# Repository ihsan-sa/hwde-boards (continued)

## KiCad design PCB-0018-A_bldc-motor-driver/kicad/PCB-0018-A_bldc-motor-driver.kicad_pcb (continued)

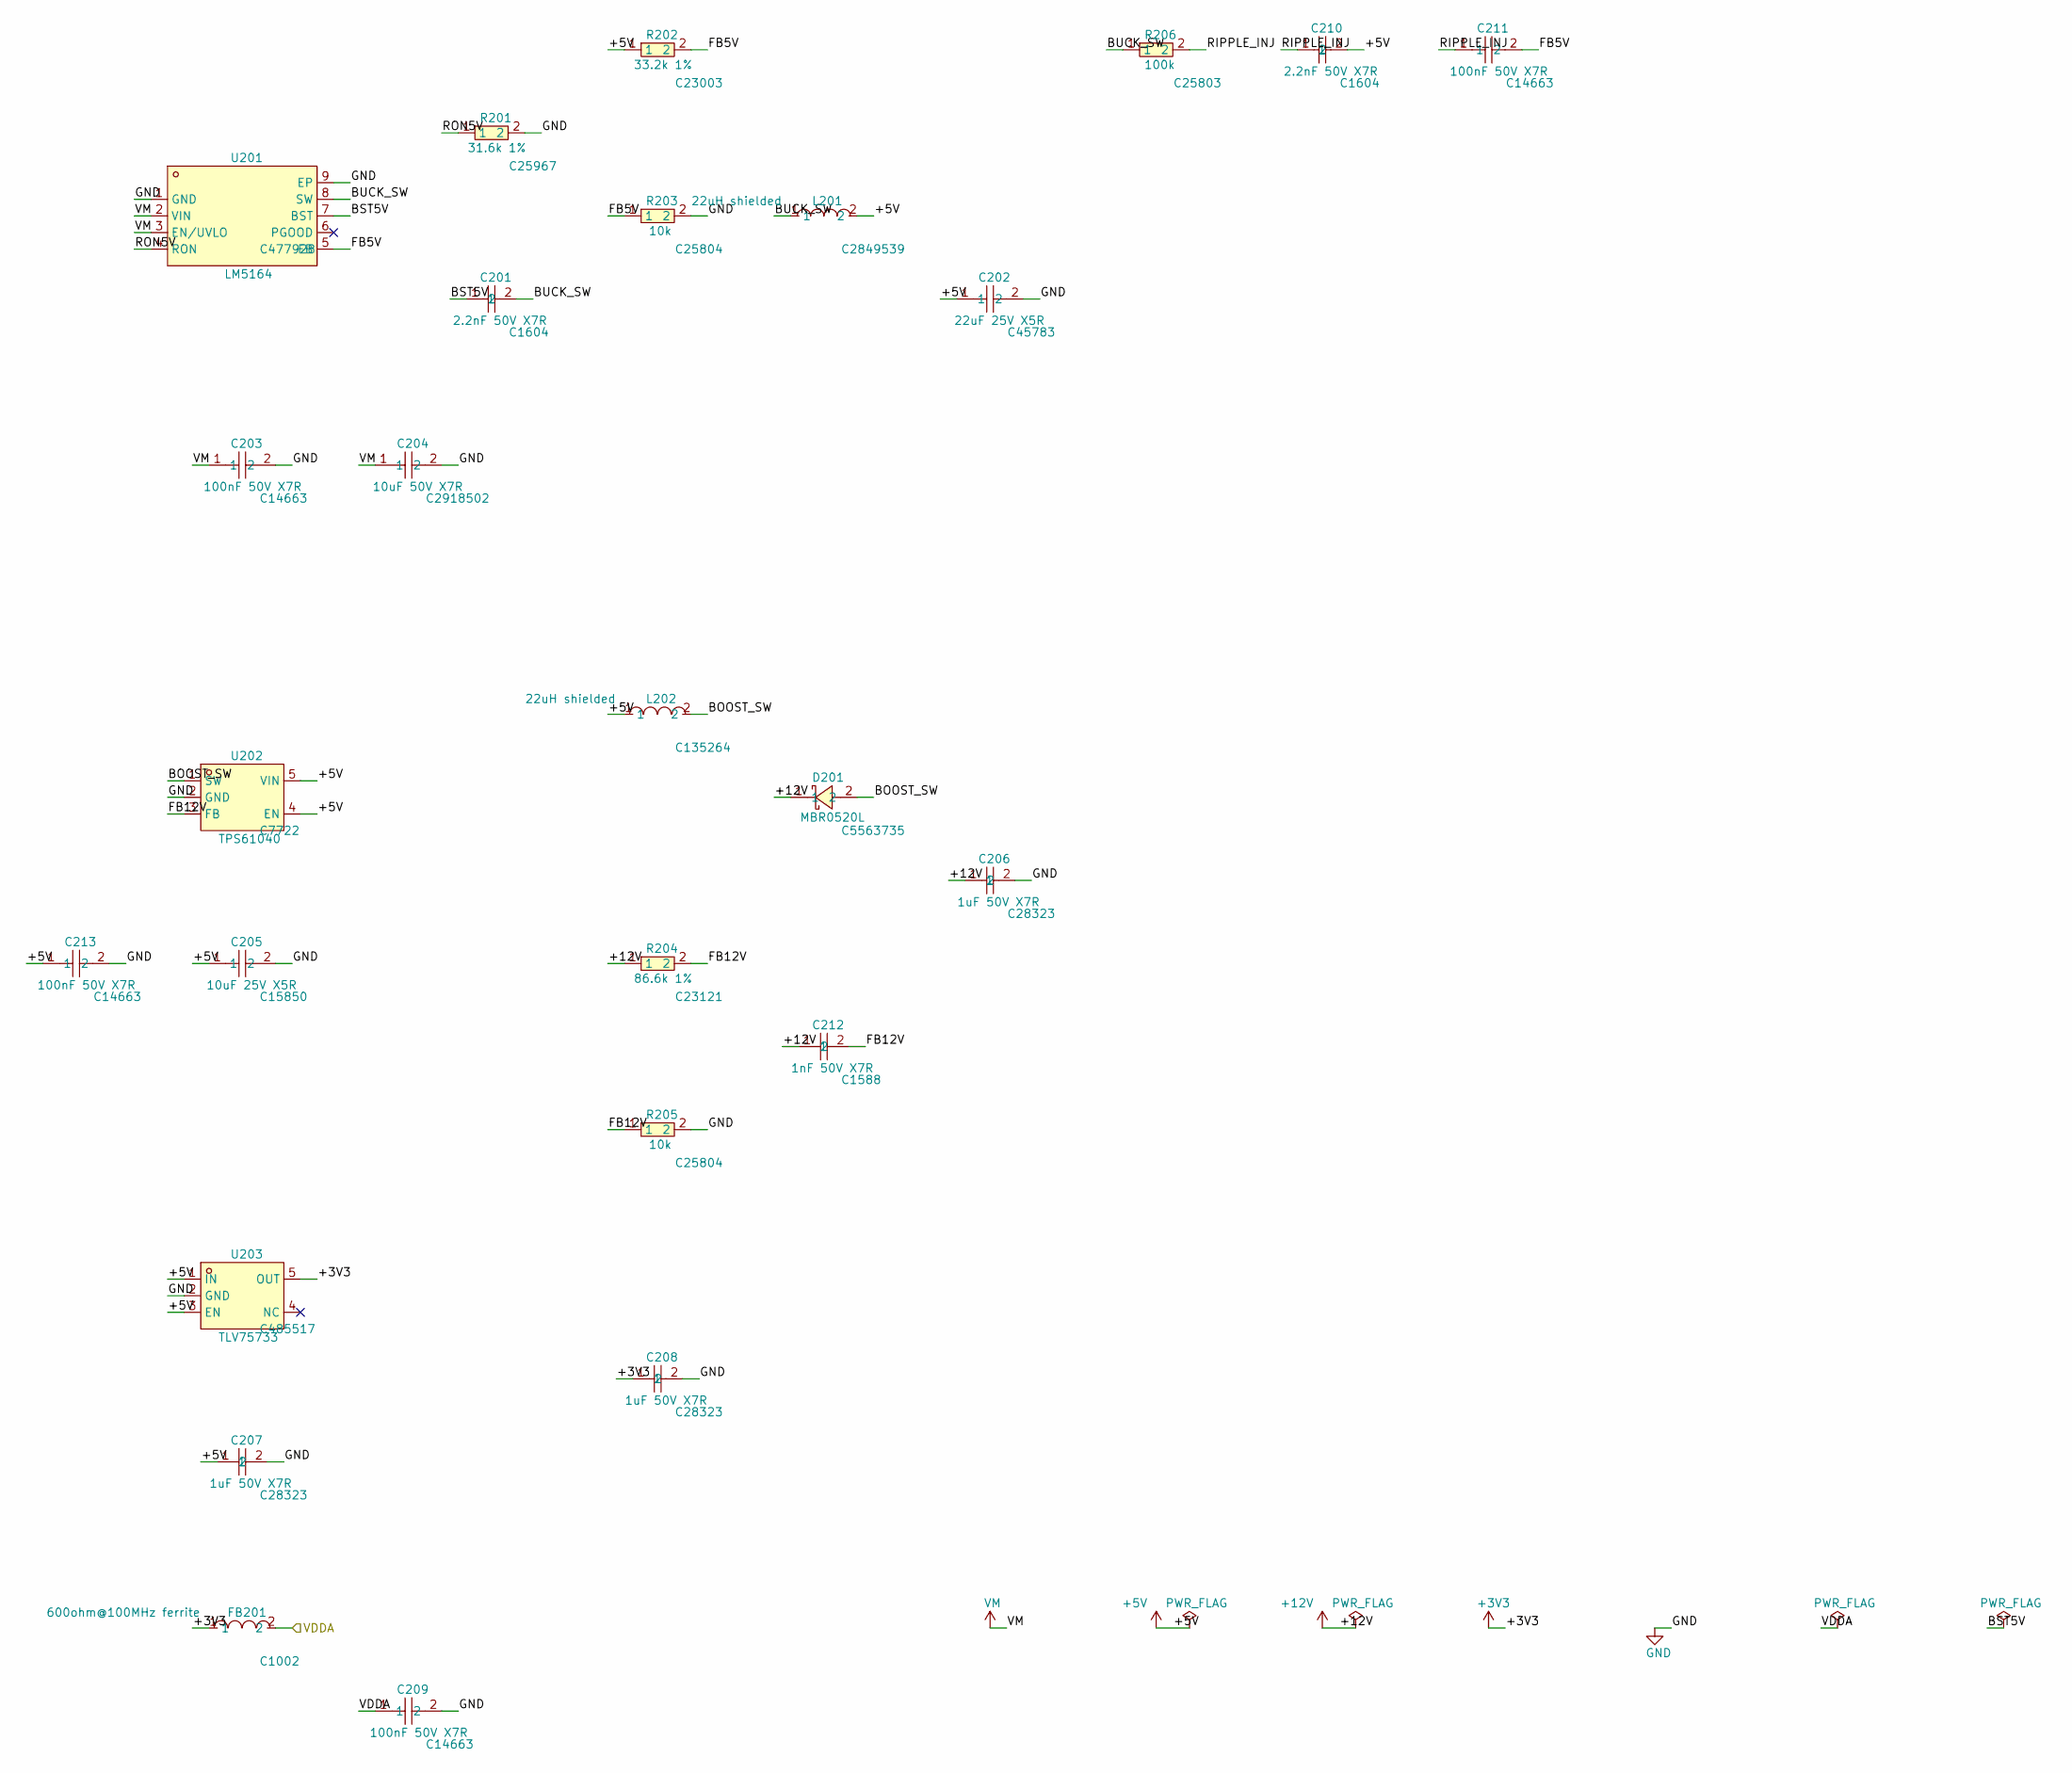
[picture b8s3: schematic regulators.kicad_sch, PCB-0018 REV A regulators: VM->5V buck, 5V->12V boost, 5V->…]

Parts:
C201, C210: 2.2nF 50V X7R; C0603; LCSC C1604
C202: 22uF 25V X5R; C0805; LCSC C45783
C203, C209, C211, C213: 100nF 50V X7R; C0603; LCSC C14663
C204: 10uF 50V X7R; C1210; LCSC C2918502
C205: 10uF 25V X5R; C0805; LCSC C15850
C206, C207, C208: 1uF 50V X7R; C0805; LCSC C28323
C212: 1nF 50V X7R; C0603; LCSC C1588
D201: MBR0520L; SOD-123_L2.7-W1.6-LS3.7-RD-1; LCSC C5563735
FB201: 600ohm@100MHz ferrite; R0603; LCSC C1002
L201: 22uH shielded; IND-SMD_L6.0-W6.0; LCSC C2849539
L202: 22uH shielded; IND-SMD_L4.0-W4.0_LQH44PN2R2MP0L; LCSC C135264
R201: 31.6k 1%; R0603; LCSC C25967
R202: 33.2k 1%; R0603; LCSC C23003
R203, R205: 10k; R0603; LCSC C25804
R204: 86.6k 1%; R0603; LCSC C23121
R206: 100k; R0603; LCSC C25803
U201: LM5164; SO-8_L4.9-W3.9-P1.27-LS6.0-BL-EP; LCSC C477928
U202: TPS61040; SOT-23-5_L2.9-W1.6-P0.95-LS2.8-BL; LCSC C7722
U203: TLV75733; SOT-23-5_L2.9-W1.6-P0.95-LS2.8-BL; LCSC C485517

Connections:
+3V3: C208.1, FB201.1, U203.5 (OUT); also elsewhere on the board
+5V: C202.1, C205.1, C207.1, C210.2, C213.1, L201.2, L202.1, R202.1, U202.4 (EN), U202.5 (VIN), U203.1 (IN), U203.3 (EN); also elsewhere on the board
+12V: C206.1, C212.1, D201.1, R204.1; also elsewhere on the board
/VDDA: C209.1, FB201.2; also elsewhere on the board
/regulators/BOOST_SW: D201.2, L202.2, U202.1 (SW)
/regulators/BST5V: C201.1, U201.7 (BST)
/regulators/BUCK_SW: C201.2, L201.1, R206.1, U201.8 (SW)
/regulators/FB5V: C211.2, R202.2, R203.1, U201.5 (FB)
/regulators/FB12V: C212.2, R204.2, R205.1, U202.3 (FB)
/regulators/RIPPLE_INJ: C210.1, C211.1, R206.2
/regulators/RON5V: R201.1, U201.4 (RON)
GND: C202.2, C203.2, C204.2, C205.2, C206.2, C207.2, C208.2, C209.2, C213.2, R201.2, R203.2, R205.2, U201.1 (GND), U201.9 (EP), U202.2 (GND), U203.2 (GND); also elsewhere on the board
VM: C203.1, C204.1, U201.2 (VIN), U201.3 (EN/UVLO); also elsewhere on the board

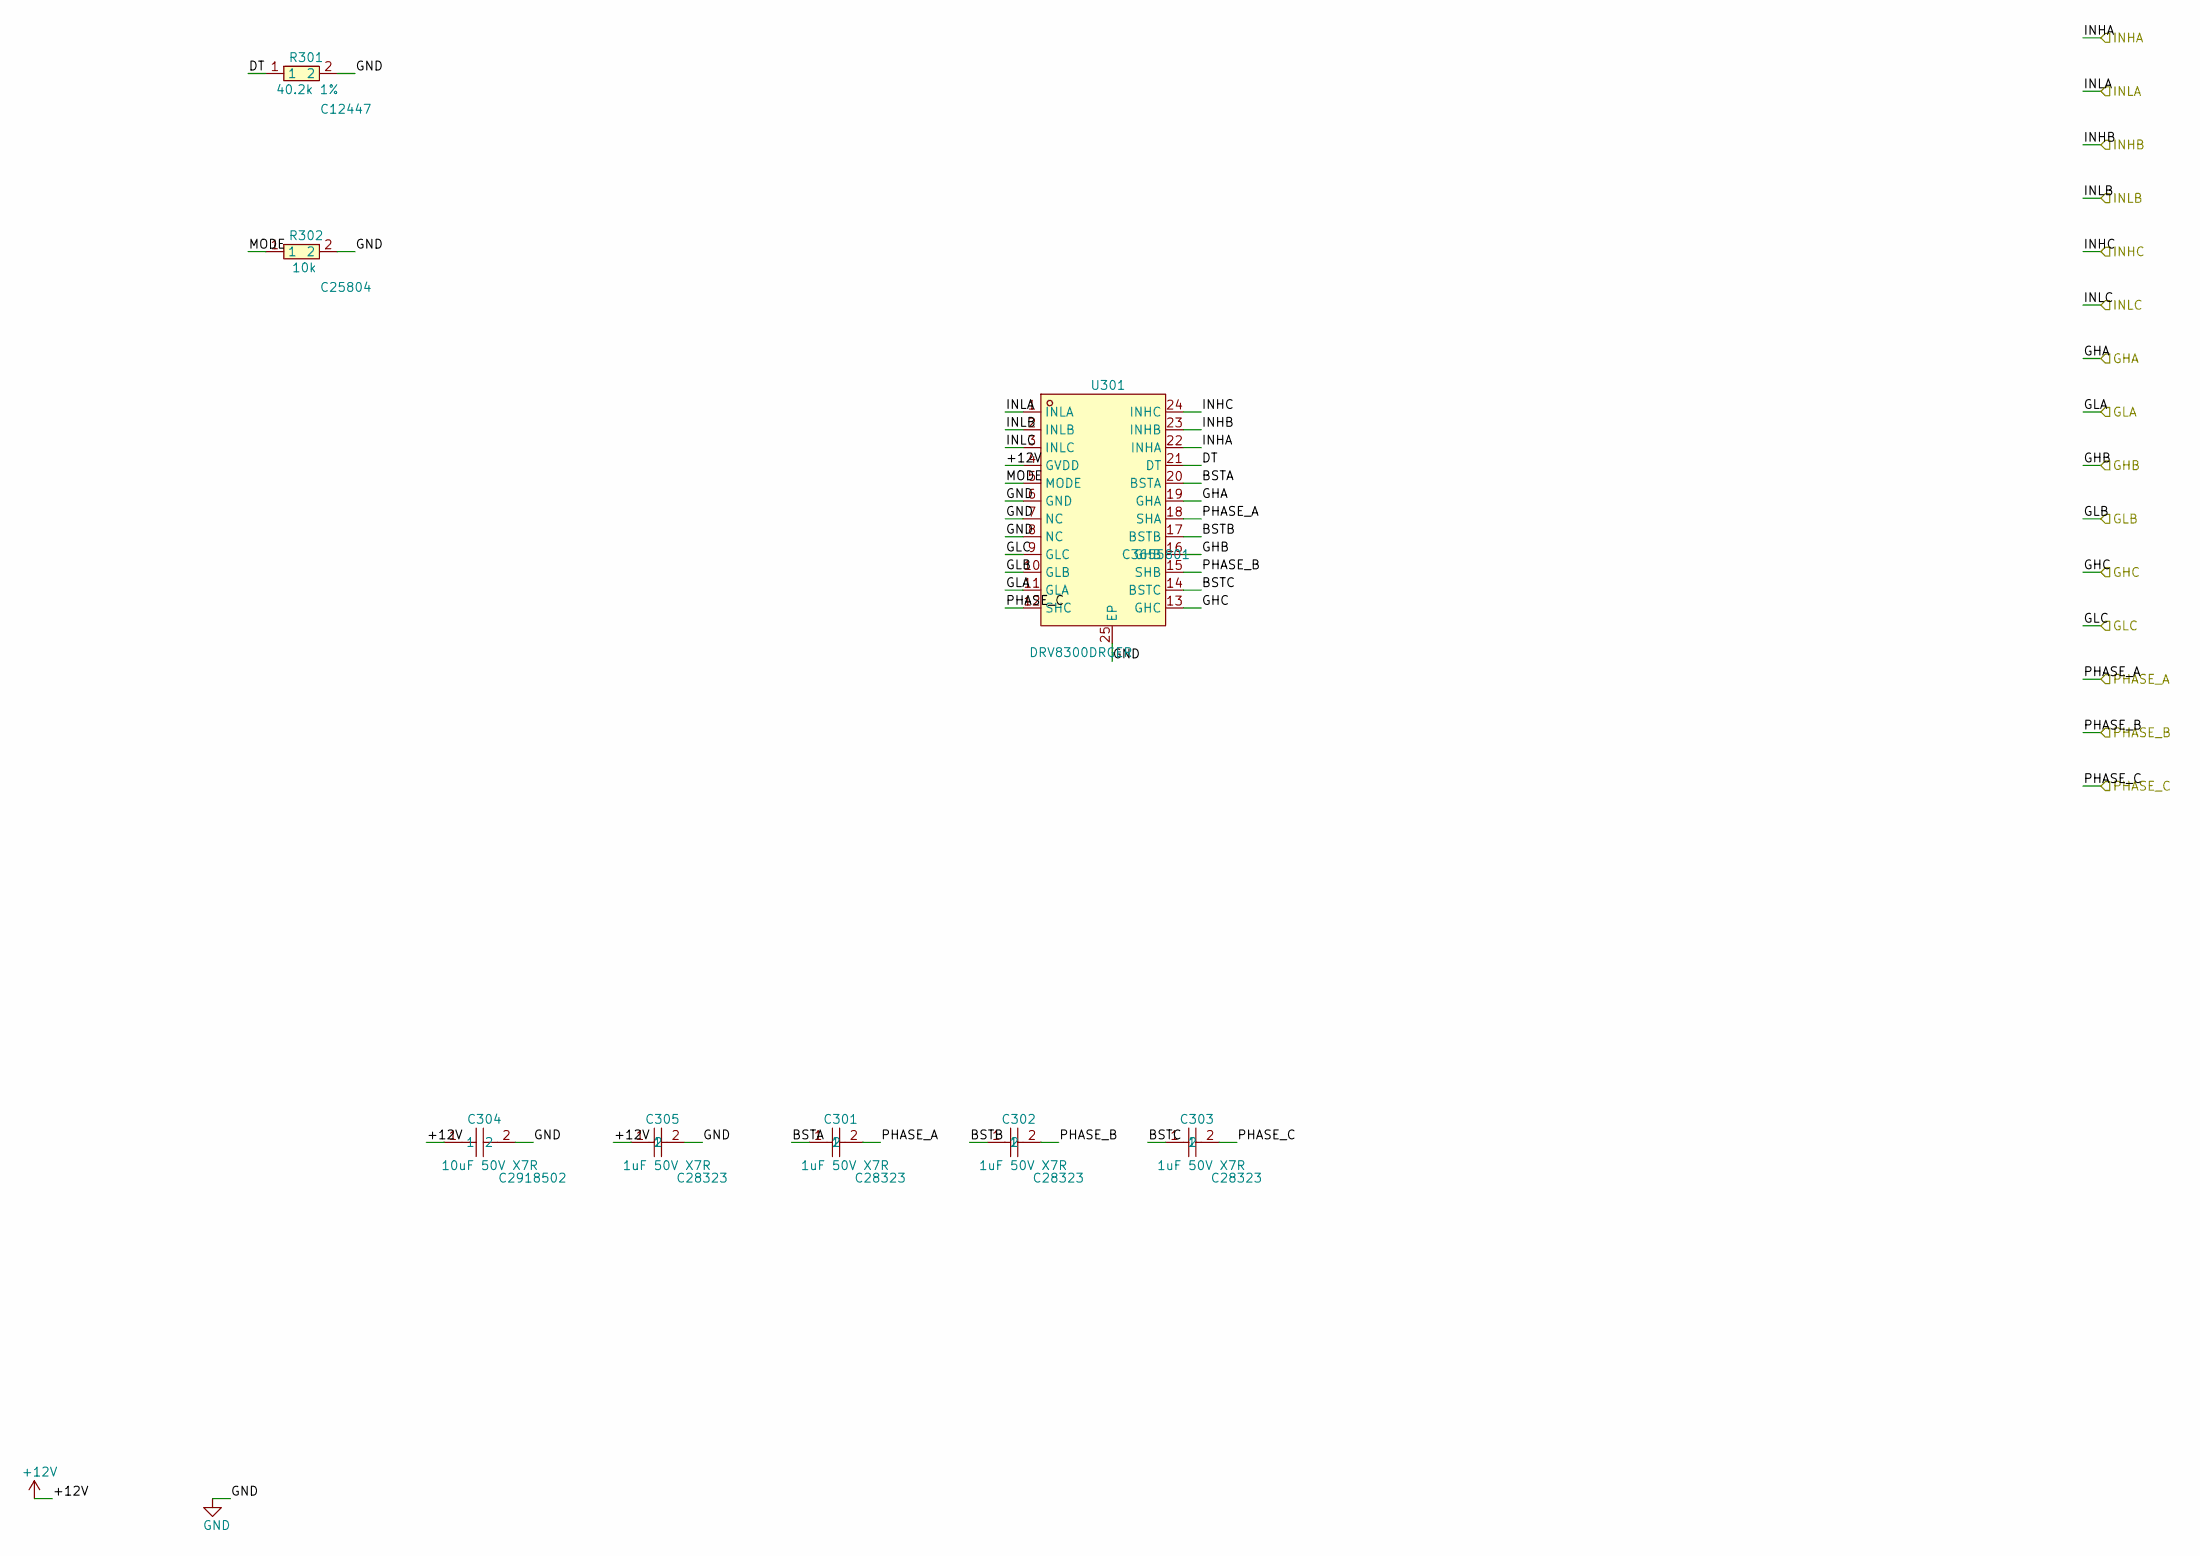
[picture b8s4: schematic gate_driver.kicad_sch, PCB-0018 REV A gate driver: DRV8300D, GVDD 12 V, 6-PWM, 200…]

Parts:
C301, C302, C303, C305: 1uF 50V X7R; C0805; LCSC C28323
C304: 10uF 50V X7R; C1210; LCSC C2918502
R301: 40.2k 1%; R0603; LCSC C12447
R302: 10k; R0603; LCSC C25804
U301: DRV8300DRGER; VQFN-24_L4.0-W4.0-P0.50-TL-EP2.5; LCSC C3655801

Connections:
+12V: C304.1, C305.1, U301.4 (GVDD); also elsewhere on the board
/GHA: U301.19 (GHA); also elsewhere on the board
/GHB: U301.16 (GHB); also elsewhere on the board
/GHC: U301.13 (GHC); also elsewhere on the board
/GLA: U301.11 (GLA); also elsewhere on the board
/GLB: U301.10 (GLB); also elsewhere on the board
/GLC: U301.9 (GLC); also elsewhere on the board
/INHA: U301.22 (INHA); also elsewhere on the board
/INHB: U301.23 (INHB); also elsewhere on the board
/INHC: U301.24 (INHC); also elsewhere on the board
/INLA: U301.1 (INLA); also elsewhere on the board
/INLB: U301.2 (INLB); also elsewhere on the board
/INLC: U301.3 (INLC); also elsewhere on the board
/PHASE_A: C301.2, U301.18 (SHA); also elsewhere on the board
/PHASE_B: C302.2, U301.15 (SHB); also elsewhere on the board
/PHASE_C: C303.2, U301.12 (SHC); also elsewhere on the board
/gate_driver/BSTA: C301.1, U301.20 (BSTA)
/gate_driver/BSTB: C302.1, U301.17 (BSTB)
/gate_driver/BSTC: C303.1, U301.14 (BSTC)
/gate_driver/DT: R301.1, U301.21 (DT)
/gate_driver/MODE: R302.1, U301.5 (MODE)
GND: C304.2, C305.2, R301.2, R302.2, U301.6 (GND), U301.7 (NC), U301.8 (NC), U301.25 (EP); also elsewhere on the board

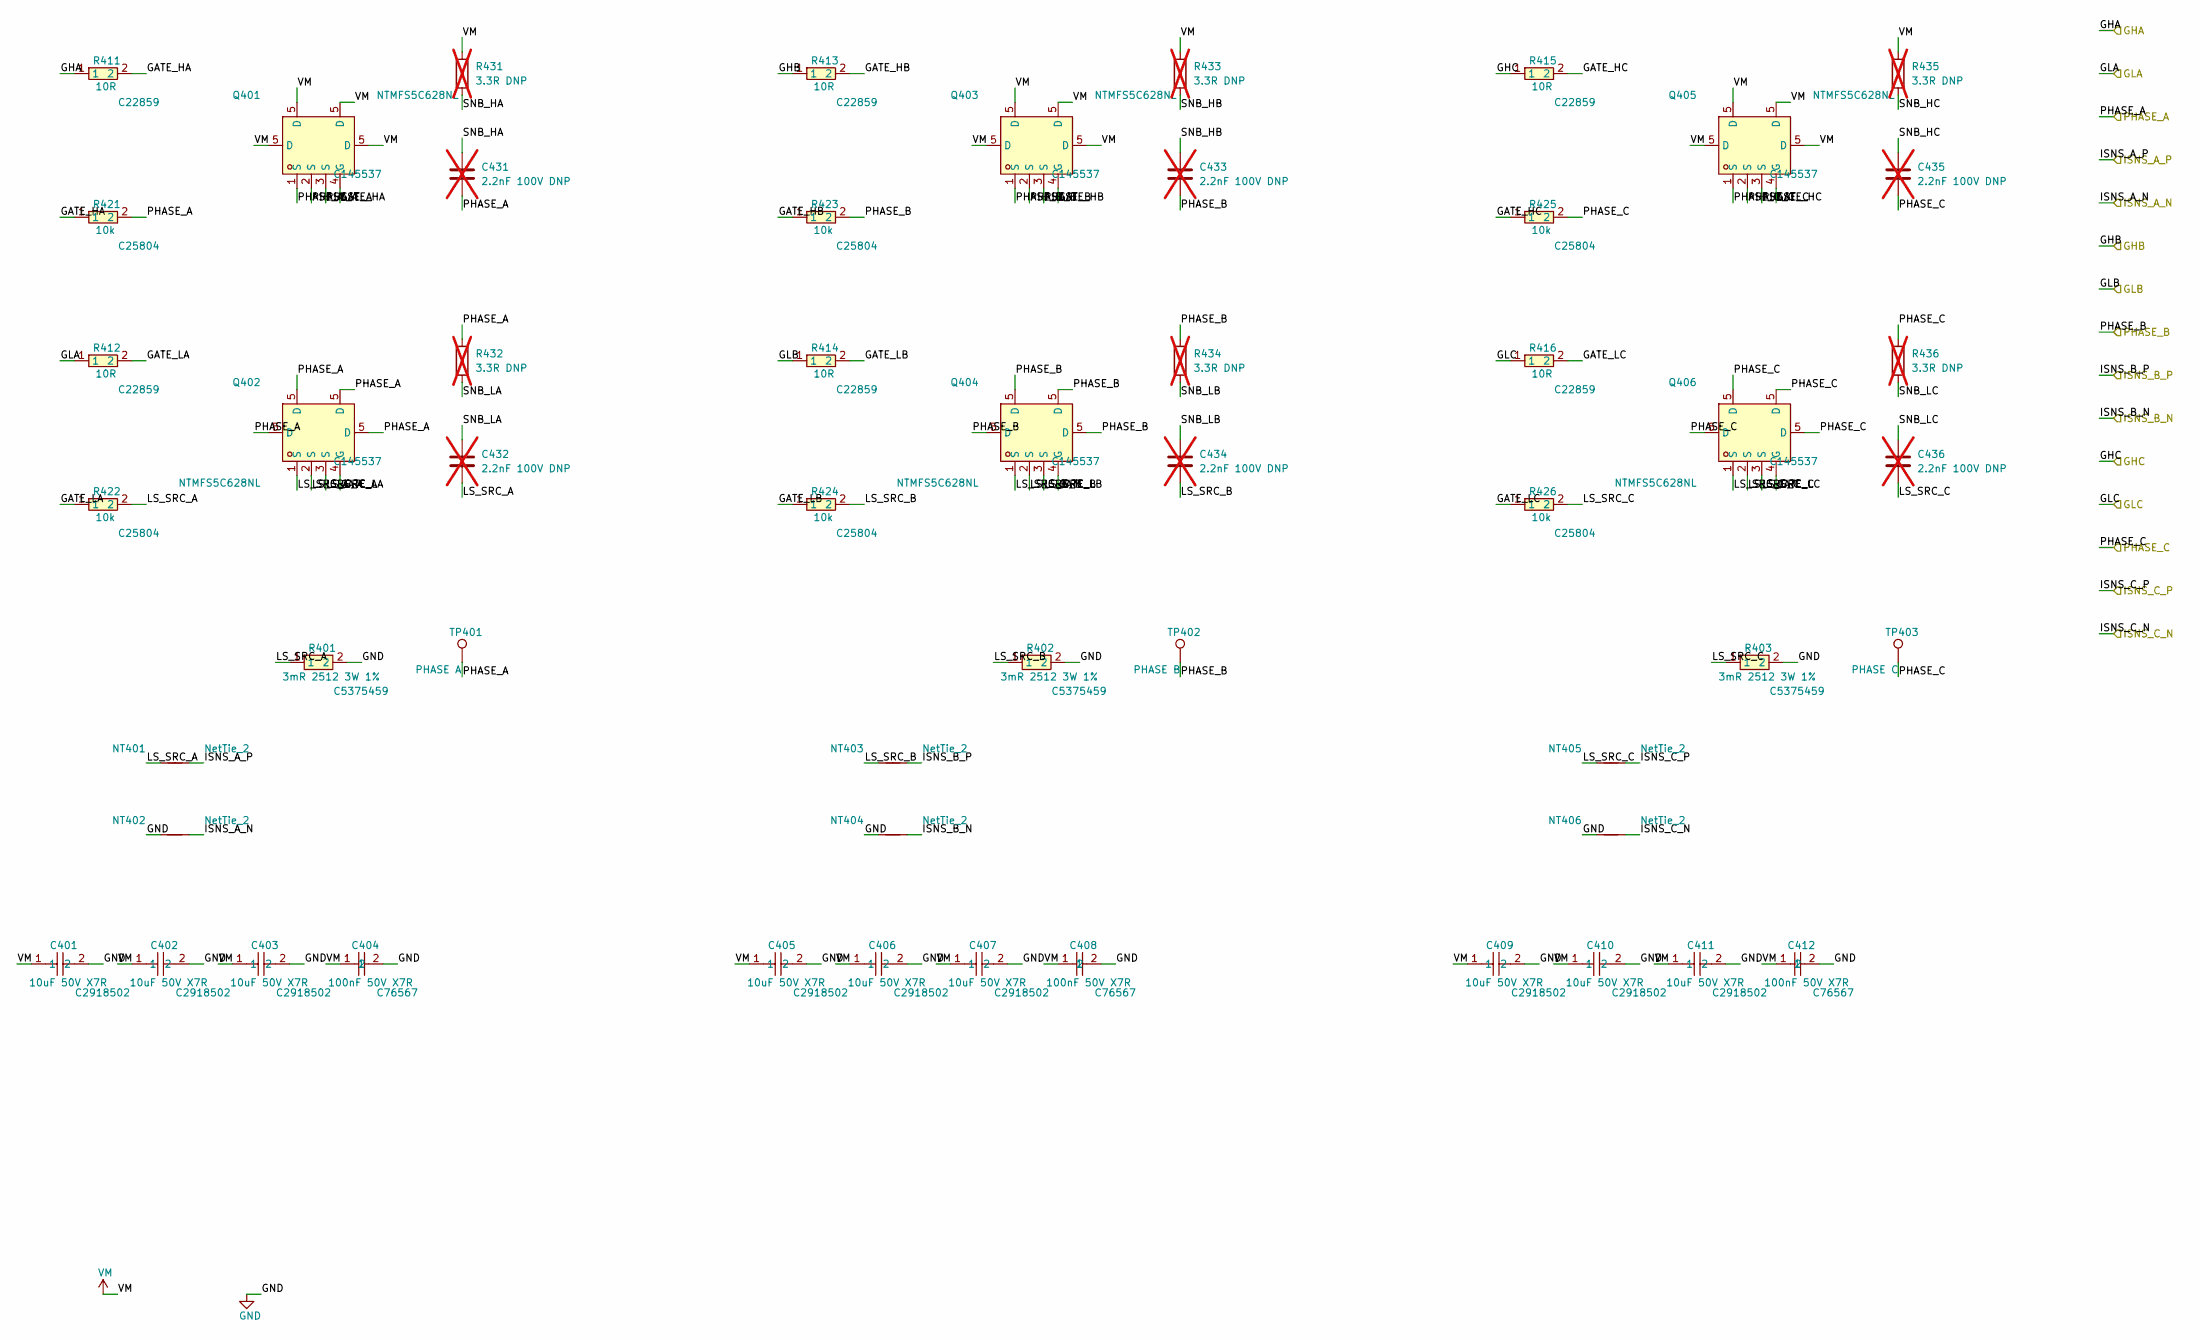
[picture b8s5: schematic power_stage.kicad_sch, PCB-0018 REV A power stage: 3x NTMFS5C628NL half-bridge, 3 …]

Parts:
C401, C402, C403, C405, C406, C407, C409, C410, C411: 10uF 50V X7R; C1210; LCSC C2918502
C404, C408, C412: 100nF 50V X7R; C1210; LCSC C76567
C431, C432, C433, C434, C435, C436: 2.2nF 100V DNP; C0603; not fitted
NT401, NT402, NT403, NT404, NT405, NT406: NetTie_2; NetTie-2_SMD_Pad0.5mm
Q401, Q402, Q403, Q404, Q405, Q406: NTMFS5C628NL; DFN-5_L4.9-W5.9-P1.27-LS6.2-BL; LCSC C145537
R401, R402, R403: 3mR 2512 3W 1%; R2512; LCSC C5375459
R411, R412, R413, R414, R415, R416: 10R; R0603; LCSC C22859
R421, R422, R423, R424, R425, R426: 10k; R0603; LCSC C25804
R431, R432, R433, R434, R435, R436: 3.3R DNP; R0603; not fitted
TP401: PHASE A; TestPoint_THTPad_4.0x4.0mm_Drill2.0mm
TP402: PHASE B; TestPoint_THTPad_4.0x4.0mm_Drill2.0mm
TP403: PHASE C; TestPoint_THTPad_4.0x4.0mm_Drill2.0mm

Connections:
/GHA: R411.1; also elsewhere on the board
/GHB: R413.1; also elsewhere on the board
/GHC: R415.1; also elsewhere on the board
/GLA: R412.1; also elsewhere on the board
/GLB: R414.1; also elsewhere on the board
/GLC: R416.1; also elsewhere on the board
/ISNS_A_N: NT402.2; also elsewhere on the board
/ISNS_A_P: NT401.2; also elsewhere on the board
/ISNS_B_N: NT404.2; also elsewhere on the board
/ISNS_B_P: NT403.2; also elsewhere on the board
/ISNS_C_N: NT406.2; also elsewhere on the board
/ISNS_C_P: NT405.2; also elsewhere on the board
/PHASE_A: C431.2, Q401.1 (S), Q401.2 (S), Q401.3 (S), Q402.5 (D), R421.2, R432.1, TP401.1; also elsewhere on the board
/PHASE_B: C433.2, Q403.1 (S), Q403.2 (S), Q403.3 (S), Q404.5 (D), R423.2, R434.1, TP402.1; also elsewhere on the board
/PHASE_C: C435.2, Q405.1 (S), Q405.2 (S), Q405.3 (S), Q406.5 (D), R425.2, R436.1, TP403.1; also elsewhere on the board
/power_stage/GATE_HA: Q401.4 (G), R411.2, R421.1
/power_stage/GATE_HB: Q403.4 (G), R413.2, R423.1
/power_stage/GATE_HC: Q405.4 (G), R415.2, R425.1
/power_stage/GATE_LA: Q402.4 (G), R412.2, R422.1
/power_stage/GATE_LB: Q404.4 (G), R414.2, R424.1
/power_stage/GATE_LC: Q406.4 (G), R416.2, R426.1
/power_stage/LS_SRC_A: C432.2, NT401.1, Q402.1 (S), Q402.2 (S), Q402.3 (S), R401.1, R422.2
/power_stage/LS_SRC_B: C434.2, NT403.1, Q404.1 (S), Q404.2 (S), Q404.3 (S), R402.1, R424.2
/power_stage/LS_SRC_C: C436.2, NT405.1, Q406.1 (S), Q406.2 (S), Q406.3 (S), R403.1, R426.2
/power_stage/SNB_HA: C431.1, R431.2
/power_stage/SNB_HB: C433.1, R433.2
/power_stage/SNB_HC: C435.1, R435.2
/power_stage/SNB_LA: C432.1, R432.2
/power_stage/SNB_LB: C434.1, R434.2
/power_stage/SNB_LC: C436.1, R436.2
GND: C401.2, C402.2, C403.2, C404.2, C405.2, C406.2, C407.2, C408.2, C409.2, C410.2, C411.2, C412.2, NT402.1, NT404.1, NT406.1, R401.2, R402.2, R403.2; also elsewhere on the board
VM: C401.1, C402.1, C403.1, C404.1, C405.1, C406.1, C407.1, C408.1, C409.1, C410.1, C411.1, C412.1, Q401.5 (D), Q403.5 (D), Q405.5 (D), R431.1, R433.1, R435.1; also elsewhere on the board

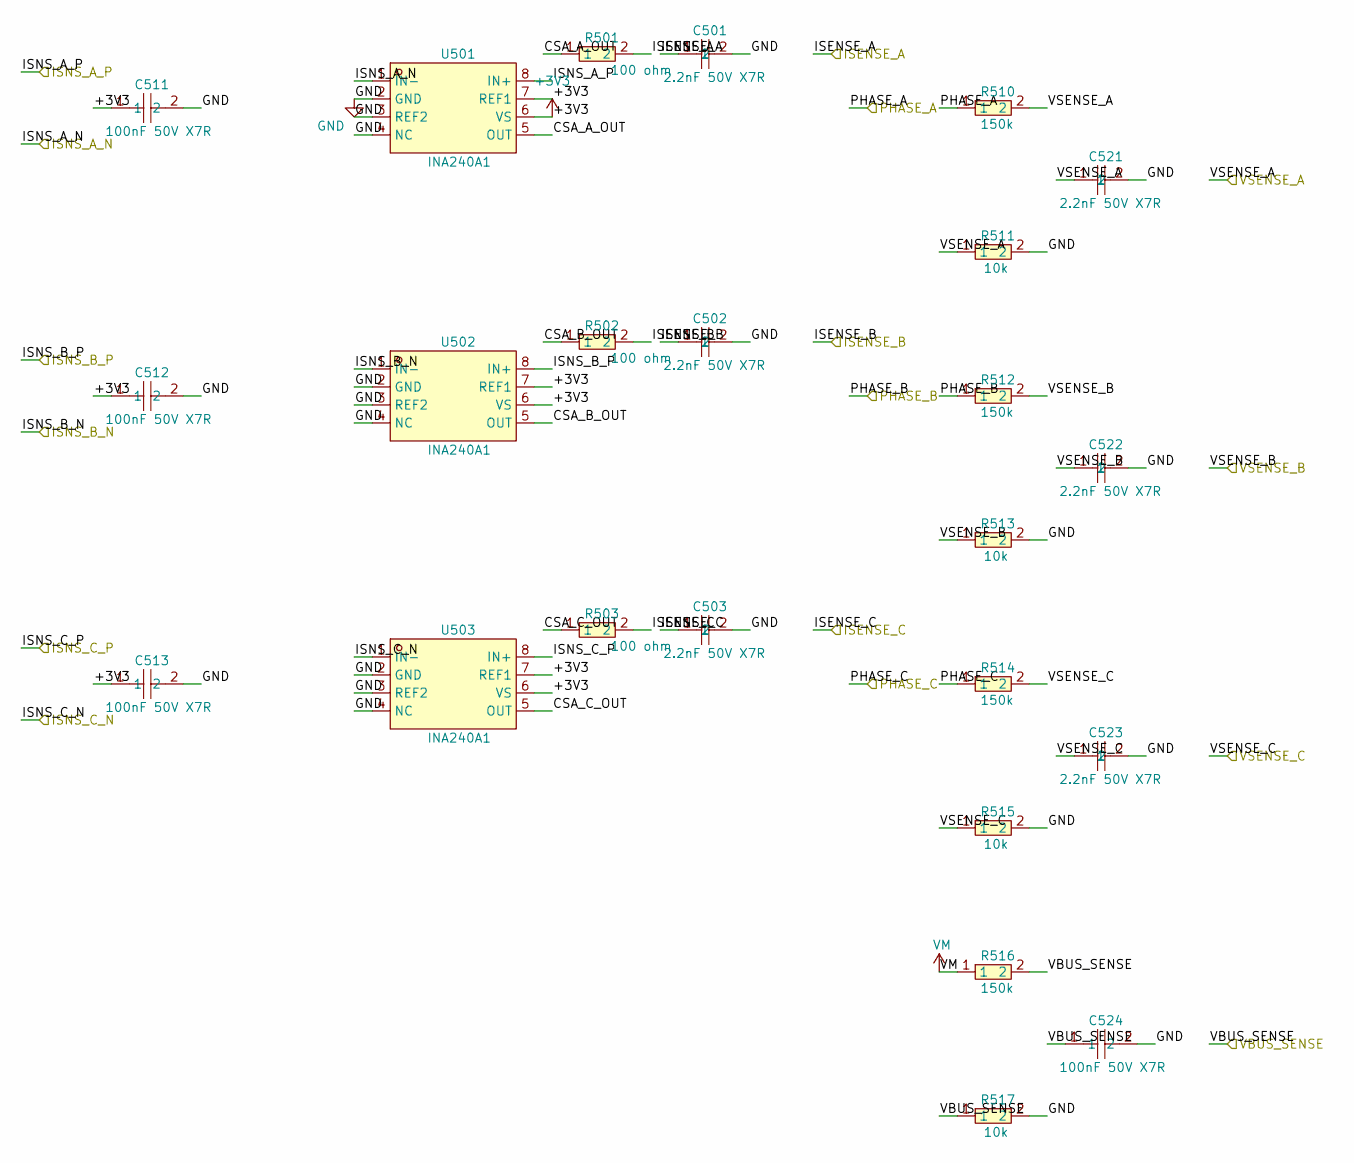
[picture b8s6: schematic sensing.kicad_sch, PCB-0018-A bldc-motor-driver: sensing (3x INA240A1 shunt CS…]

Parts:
C501, C502, C503, C521, C522, C523: 2.2nF 50V X7R; C0603; LCSC C1604
C511, C512, C513, C524: 100nF 50V X7R; C0603; LCSC C14663
R501, R502, R503: 100 ohm; R0603; LCSC C22775
R510, R512, R514, R516: 150k; R0603; LCSC C22807
R511, R513, R515, R517: 10k; R0603; LCSC C25804
U501, U502, U503: INA240A1; SOIC-8_L5.0-W4.0-P1.27-LS6.0-BL; LCSC C2060769

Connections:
+3V3: C511.1, C512.1, C513.1, U501.6 (VS), U501.7 (REF1), U502.6 (VS), U502.7 (REF1), U503.6 (VS), U503.7 (REF1); also elsewhere on the board
/ISENSE_A: C501.1, R501.2; also elsewhere on the board
/ISENSE_B: C502.1, R502.2; also elsewhere on the board
/ISENSE_C: C503.1, R503.2; also elsewhere on the board
/ISNS_A_N: U501.1 (IN-); also elsewhere on the board
/ISNS_A_P: U501.8 (IN+); also elsewhere on the board
/ISNS_B_N: U502.1 (IN-); also elsewhere on the board
/ISNS_B_P: U502.8 (IN+); also elsewhere on the board
/ISNS_C_N: U503.1 (IN-); also elsewhere on the board
/ISNS_C_P: U503.8 (IN+); also elsewhere on the board
/PHASE_A: R510.1; also elsewhere on the board
/PHASE_B: R512.1; also elsewhere on the board
/PHASE_C: R514.1; also elsewhere on the board
/VBUS_SENSE: C524.1, R516.2, R517.1; also elsewhere on the board
/VSENSE_A: C521.1, R510.2, R511.1; also elsewhere on the board
/VSENSE_B: C522.1, R512.2, R513.1; also elsewhere on the board
/VSENSE_C: C523.1, R514.2, R515.1; also elsewhere on the board
/sensing/CSA_A_OUT: R501.1, U501.5 (OUT)
/sensing/CSA_B_OUT: R502.1, U502.5 (OUT)
/sensing/CSA_C_OUT: R503.1, U503.5 (OUT)
GND: C501.2, C502.2, C503.2, C511.2, C512.2, C513.2, C521.2, C522.2, C523.2, C524.2, R511.2, R513.2, R515.2, R517.2, U501.2 (GND), U501.3 (REF2), U501.4 (NC), U502.2 (GND), U502.3 (REF2), U502.4 (NC), U503.2 (GND), U503.3 (REF2), U503.4 (NC); also elsewhere on the board
VM: R516.1; also elsewhere on the board

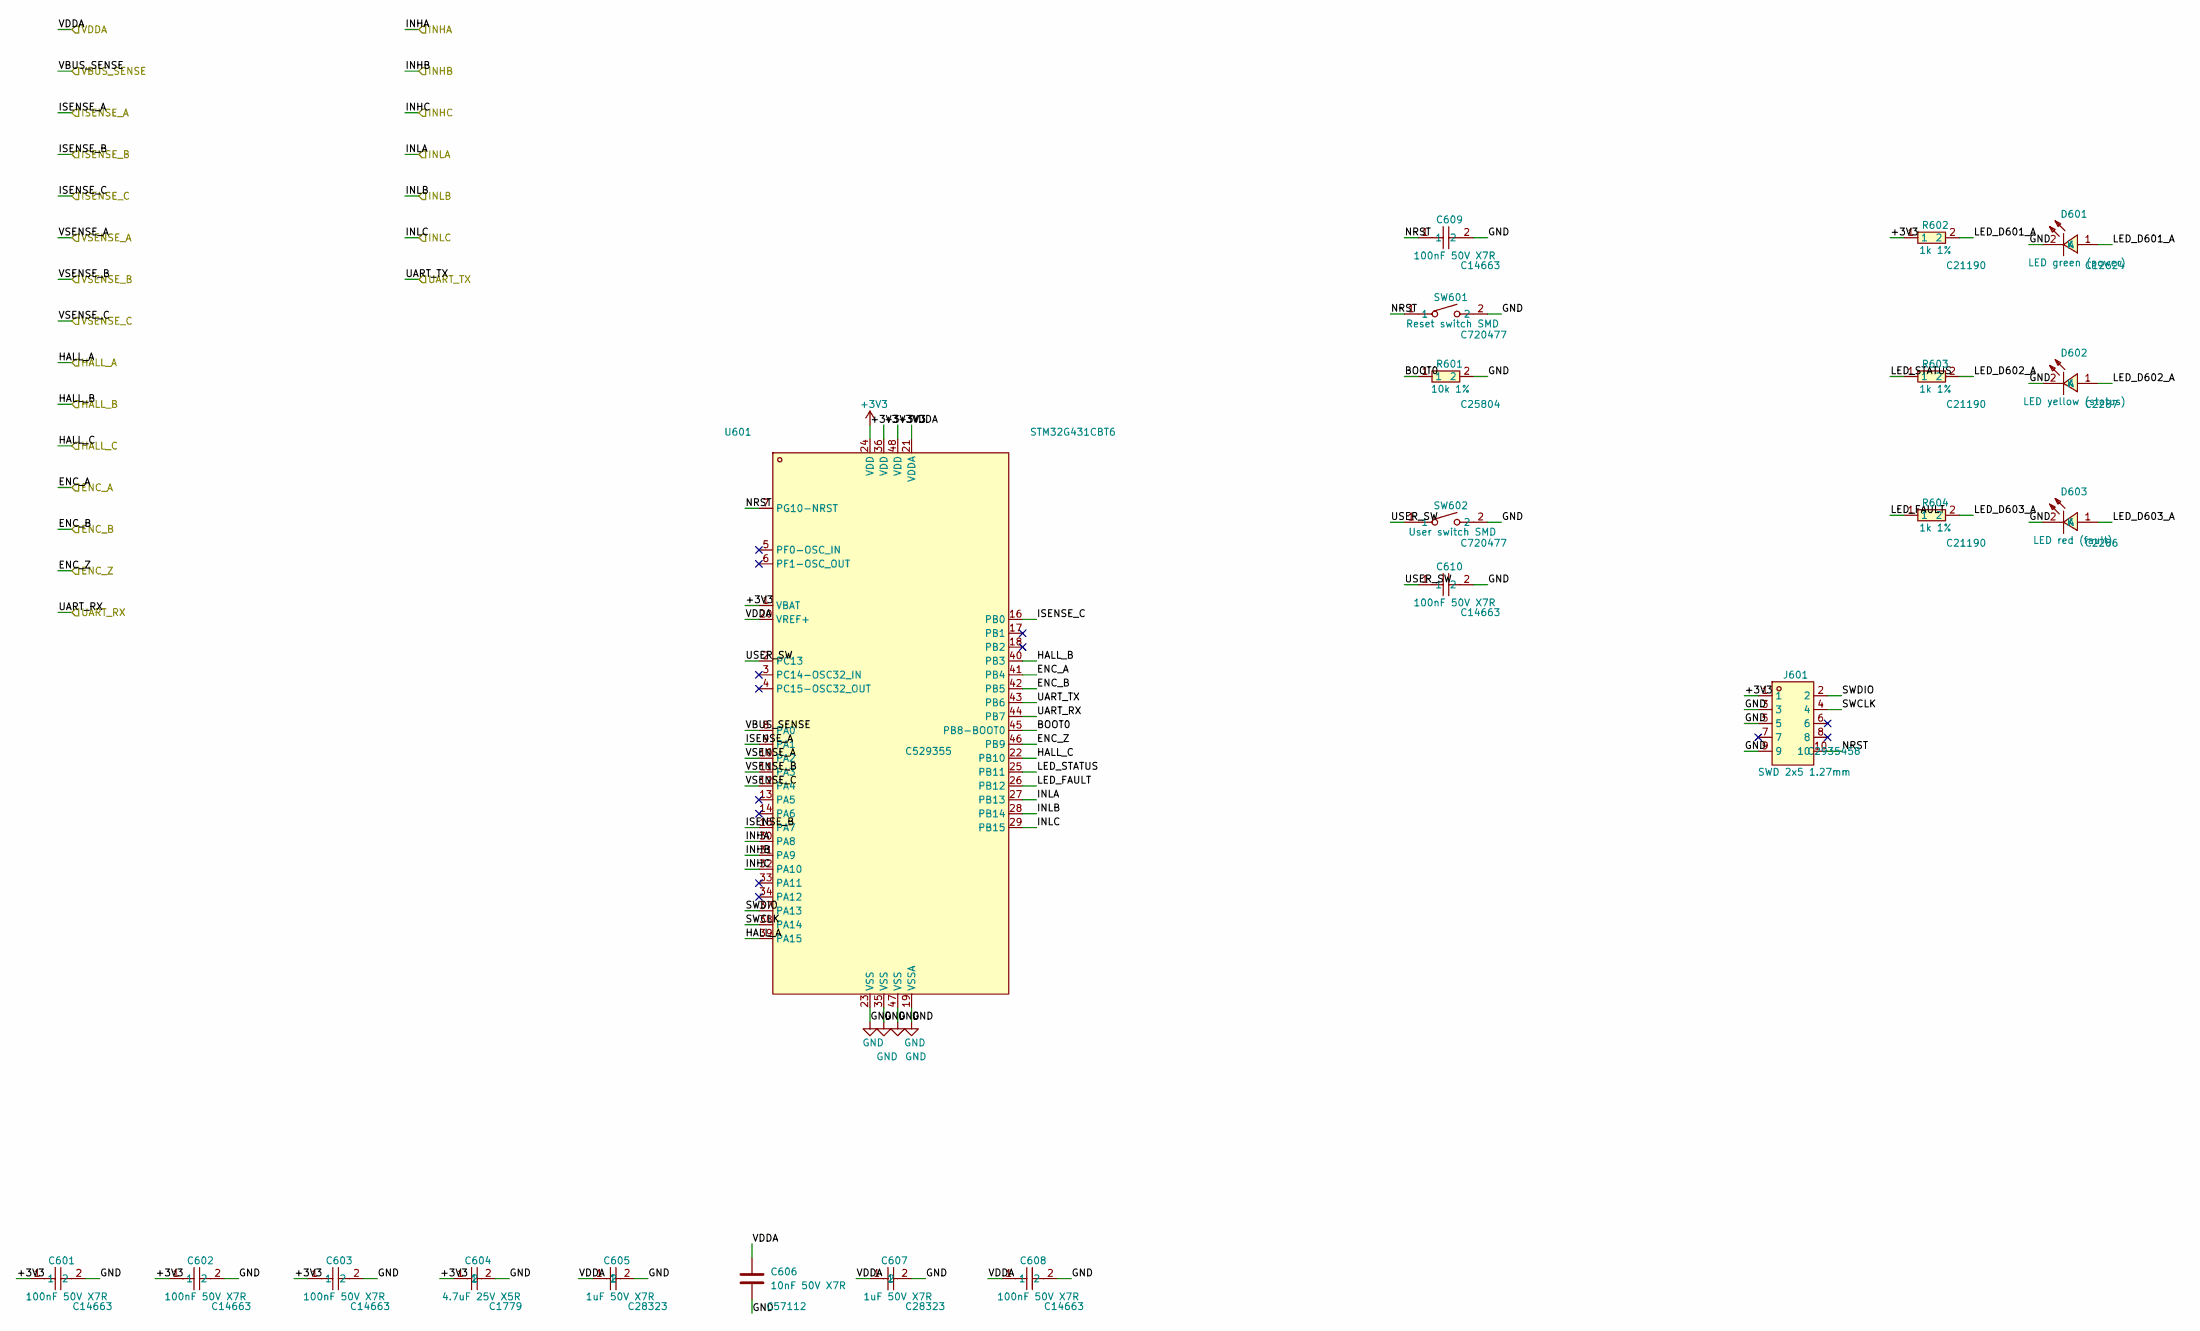
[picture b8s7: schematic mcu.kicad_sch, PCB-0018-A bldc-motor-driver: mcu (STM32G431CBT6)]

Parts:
C601, C602, C603, C608, C609, C610: 100nF 50V X7R; C0603; LCSC C14663
C604: 4.7uF 25V X5R; C0805; LCSC C1779
C605, C607: 1uF 50V X7R; C0805; LCSC C28323
C606: 10nF 50V X7R; C0603; LCSC C57112
D601: LED green (power); LED-SMD_L1.6-W0.8-R-RD; LCSC C12624
D602: LED yellow (status); LED-SMD_L1.6-W0.8-R-RD; LCSC C2287
D603: LED red (fault); LED-SMD_L1.6-W0.8-R-RD; LCSC C2286
J601: SWD 2x5 1.27mm; CONN-SMD_10P-P1.27_XFCN_PZ127VS-12-10-H10-A38; LCSC C2935458
R601: 10k 1%; R0603; LCSC C25804
R602, R603, R604: 1k 1%; R0603; LCSC C21190
SW601: Reset switch SMD; SW-SMD_L3.9-W3.0-P4.45; LCSC C720477
SW602: User switch SMD; SW-SMD_L3.9-W3.0-P4.45; LCSC C720477
U601: STM32G431CBT6; LQFP-48_L7.0-W7.0-P0.50-LS9.0-BL; LCSC C529355

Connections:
+3V3: C601.1, C602.1, C603.1, C604.1, J601.1, R602.1, U601.1 (VBAT), U601.24 (VDD), U601.36 (VDD), U601.48 (VDD); also elsewhere on the board
/ENC_A: U601.41 (PB4); also elsewhere on the board
/ENC_B: U601.42 (PB5); also elsewhere on the board
/ENC_Z: U601.46 (PB9); also elsewhere on the board
/HALL_A: U601.39 (PA15); also elsewhere on the board
/HALL_B: U601.40 (PB3); also elsewhere on the board
/HALL_C: U601.22 (PB10); also elsewhere on the board
/INHA: U601.30 (PA8); also elsewhere on the board
/INHB: U601.31 (PA9); also elsewhere on the board
/INHC: U601.32 (PA10); also elsewhere on the board
/INLA: U601.27 (PB13); also elsewhere on the board
/INLB: U601.28 (PB14); also elsewhere on the board
/INLC: U601.29 (PB15); also elsewhere on the board
/ISENSE_A: U601.9 (PA1); also elsewhere on the board
/ISENSE_B: U601.15 (PA7); also elsewhere on the board
/ISENSE_C: U601.16 (PB0); also elsewhere on the board
/UART_RX: U601.44 (PB7); also elsewhere on the board
/UART_TX: U601.43 (PB6); also elsewhere on the board
/VBUS_SENSE: U601.8 (PA0); also elsewhere on the board
/VDDA: C605.1, C606.1, C607.1, C608.1, U601.20 (VREF+), U601.21 (VDDA); also elsewhere on the board
/VSENSE_A: U601.10 (PA2); also elsewhere on the board
/VSENSE_B: U601.11 (PA3); also elsewhere on the board
/VSENSE_C: U601.12 (PA4); also elsewhere on the board
/mcu/BOOT0: R601.1, U601.45 (PB8-BOOT0)
/mcu/LED_D601_A: D601.1 (A), R602.2
/mcu/LED_D602_A: D602.1 (A), R603.2
/mcu/LED_D603_A: D603.1 (A), R604.2
/mcu/LED_FAULT: R604.1, U601.26 (PB12)
/mcu/LED_STATUS: R603.1, U601.25 (PB11)
/mcu/NRST: C609.1, J601.10, SW601.1, U601.7 (PG10-NRST)
/mcu/SWCLK: J601.4, U601.38 (PA14)
/mcu/SWDIO: J601.2, U601.37 (PA13)
/mcu/USER_SW: C610.1, SW602.1, U601.2 (PC13)
GND: C601.2, C602.2, C603.2, C604.2, C605.2, C606.2, C607.2, C608.2, C609.2, C610.2, D601.2 (K), D602.2 (K), D603.2 (K), J601.3, J601.5, J601.9, R601.2, SW601.2, SW602.2, U601.19 (VSSA), U601.23 (VSS), U601.35 (VSS), U601.47 (VSS); also elsewhere on the board
